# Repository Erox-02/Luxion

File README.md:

# Luxion

Luxion is a custom made drone made with rust unlike standard c++ drones .
It uses a custom pcb, ESP32-S3-WROOM-1U , MPU6500-IMU(breakout as it costs less than the bare), four motor drivers, and a 1S LiPo to power the drone. Also a remote with
same esp module, 2x joysticks connectin to the drone via esp-now .

## Function

It is a remote controlled drone made from absolutely nothing , with 8520 motors and 65mm props it can easily take off with 2+ thrust-mass ratio . It is ideal for mini quadcoptor with mountable sensors ,as it has a lot of gpio's left any sensor can be easily mounted if not too heavy .

## Why it exists

from when i saw the pluto x  , a programable drone with esp 12f and stm32 , i always wanted to make one myself but better and cheaper thts why luxion exists today. I used esp32-s3 instead of 2 mcu's , used esp-now instead of wifi and a lot but the best part i didnt rely on the pluto x's architecture at all .

## Design
---

### 3D Model

> **Notice: All the screws there are 3mm .** 

The recommended range by me is M5x3 mm 

heres a photo tagged:

but for the pcb M1.2x3 mm is totally usable 

#### Drone

You can download the 3d model frm here :
[DOWNLOAD THE 3d MODEL](3d/lux.3mf)

also the  fcstd file is tagged here :

[FCSTD](3d/lux.FCStd)

some photos for the frame :

<table>
  <tr>
    <td></td>
    <td></td>
    <td></td>
  </tr>
</table>

---

#### Remote

You can download the 3d model frm here :

[DOWNLOAD THE 3d MODEL](3d/remote-body.3mf)
[DOWNLOAD THE 3d MODEL](3d/remote-lid.3mf)

===

also the  fcstd file is tagged here :

[FCSTD](3d/remote.FCStd)

Some phots of the remote :

<table>
  <tr>
    <td></td>
    <td></td>
  </tr>
</table>

---

### Schematic
---

#### drone

<table>
  <tr>
    <td></td>
    <td></td>
    <td></td>
  </tr>
  <tr>
    <td></td>
    <td></td>
    <td></td>
  </tr>
  <tr>
    <td></td>
    <td></td>
  </tr>
</table>

---

#### remote
---

<table>
  <tr>
    <td></td>
    <td></td>
  </tr>
  <tr>
    <td></td>
    <td></td>
  </tr>
</table>

### PCB

#### drone

Heres the pcb :

<table>
  <tr>
    <td></td>
    <td></td>
  </tr>
</table>

#### remote

Heres the pcb :

<table>
  <tr>
    <td></td>
    <td></td>
  </tr>
</table>

## Firmware

I have written likely most of the firmware already before getting approved or building the physical drone .

Current stack have :
```
[erox@archbtw luxion]$ tree src 
src
├── filter.rs
├── main.rs
├── motor.rs
├── mpu.rs          
└── pid.rs

1 directory, 5 files
```

the mpu.rs is a custom driver(really basic) for the mpu6050 , the filte* take mpu's data(gyro and acc) then converts tht into yaw roll and pitch , the moto* haved ldec and controlls the motors state , the pid is just pid controller nothing more , and the main.rs integrates them all and runs them when needed either in loop or once .

### Whats remainin?

- esp now impl
- build.rs
- proper pid vals and calibration

## How to assemble

Solder all the components from bom(except the antenna) on the pcb ,
also You might need to solder a jst socket according to your battery
(more detailed explanation after i do it myself first lol)

you can follow this hand drawn diagram(even orphy is better than me)
---

---

another thing to consider, this photo doesnt have all the components placed so this isnt the final pcb(checkt he comps on bom ) , and for the mpu6050 and the bmp , they are supposed to be placed horizontal to the pcb , mpu on the esp farday cage(tested by max imagination, he is a cool dude btw , i saw his Arduino drone on YouTube) and the bmp shld be stacked on top of mpu , it shld give them the least vibration err , still idea but i will be sure after i build it myself lol.

## Credits

This project uses:

- KiCad
- Freecad for 3D renders
- A opensource frame from the link below

[link](https://www.thingiverse.com/thing:5013951)

> It was the reference for my frame i had to rebuild it .

## JLCPCB order

---

---

> the price might fluctuate over time

## BOM

| Part | Quantity | Unit Price (INR) | Unit Price (USD) | Total (INR) | Total (USD) | Link |
|---|---:|---:|---:|---:|---:|---|
| MPU-6050 3-Axis Accelerometer + Gyro | 1 | 151.00 | 1.59 | 151.00 | 1.59 | [Link](https://robu.in/product/mpu-6050-gyro-sensor-2-accelerometer/) |
| PS2 Joystick Module Breakout Sensor | 2 | 39.00 | 0.41 | 78.00 | 0.82 | [Link](https://robu.in/product/joystick-module-ps2-breakout-sensor/) |
| 8520 Magnetic Micro Coreless Motors – 2xCW + 2xCCW pack | 1 | 459.00 | 4.83 | 459.00 | 4.83 | [Link](https://robu.in/product/8520-magnetic-micro-coreless-motor-for-micro-quadcopters-2xcw-2xccw/) |
| 100kΩ 0603 resistor (MOQ) | 30 | 0.34 | 0.004 | 10.20 | 0.11 | [Link](https://robu.in/product/100k-ohm-1-4w-0603-surface-mount-chip-resistor-pack-of-100/) |
| 220Ω 0603 resistor (MOQ) | 30 | 0.34 | 0.004 | 10.20 | 0.11 | [Link](https://robu.in/product/220-ohm-chip-resistor-1-4w-0603-surface-mount-pack-of-100/) |
| 3V Active Electromagnetic Buzzer – pack of 5 | 1 | 21.00 | 0.22 | 21.00 | 0.22 | [Link](https://robu.in/product/3v-active-electromagnetic-buzzer-pack-of-5/) |
| 1206 Surface Mount LED White (MOQ) | 10 | 1.07 | 0.011 | 10.70 | 0.11 | [Link](https://robu.in/product/1206-surface-mount-led-white-50-pcs/) |
| 1206 Surface Mount LED Yellow (MOQ) | 25 | 0.40 | 0.004 | 10.00 | 0.11 | [Link](https://robu.in/product/1206-surface-mount-led-yellow-50pcs/) |
| BMP180 Digital Barometric Pressure Sensor Module | 1 | 33.00 | 0.35 | 33.00 | 0.35 | [Link](https://robu.in/product/bmp180-digital-barometric-pressure-sensor-module/) |
| LWC-2400-DIP-03 (V1.0) Dipole Antenna 2.4 GHz | 2 | 132.00 | 1.39 | 264.00 | 2.78 | [Link](https://robu.in/product/lwc-2400-dip-03-v1-0-dipole-antennas-2-4-ghz/) |
| Bonka 3.7V 600mAh 25C 1S LiPo | 1 | 499.00 | 5.25 | 499.00 | 5.25 | [Link](https://robu.in/product/bonka-3-7v-600mah-25c-1s-lithium-polymer-battery-pack/) |
| 22µF 16V 1206 X5R capacitor (MOQ) | 28 | 0.36 | 0.004 | 10.08 | 0.11 | [Link](https://robu.in/product/1206x226k160ct-samsung-smd-multilayer-ceramic-capacitor-22-%c2%b5f-16-v-1206-3216-metric-%c2%b1-10-x5r/) |
| 100nF 0402 X7R capacitor (MOQ) | 100 | 0.10 | 0.001 | 10.00 | 0.11 | [Link](https://robu.in/product/im02b104k250nb-fh-smd-multilayer-ceramic-capacitor-0-1-%c2%b5f100-nf-25-v-0402-1005-metric-%c2%b1-10-x7r-cl/) |
| 10kΩ 0603 resistor (MOQ) | 15 | 0.68 | 0.007 | 10.20 | 0.11 | [Link](https://robu.in/product/ac0603fr-0710kl-yageo-res-thick-film-0603-10k-ohm-1-0-1w1-10w-%c2%b1100ppm-c-pad-smd-t-r-automotive-aec-q200/) |
| ESP32-S3-WROOM-1U-N16R8 | 2 | 469.00 | 4.94 | 938.00 | 9.87 | [Link](https://robu.in/product/espressif-esp32-s3-wroom-1u-n16r8-module/) |
| 10µF 10V 0805 X5R capacitor (MOQ) | 22 | 0.47 | 0.005 | 10.34 | 0.11 | [Link](https://robu.in/product/cs2012x5r106m100nre-samwha-10v-x5r-0805-multilayer-ceramic-capacitors-mlcc-smd-smt-rohs/) |
| SRN8040-1R5Y 1.5µH 7A inductor | 1 | 23.00 | 0.24 | 23.00 | 0.24 | [Link](https://robu.in/product/srn8040-1r5y-bourns-srn8040-1r5y-power-inductor-smd-1-5-%c2%b5h-7-a-shielded-8-2-a-srn8040-series/) |
| BL5612-BL H-Bridge Motor Driver IC | 4 | 41.00 | 0.43 | 164.00 | 1.73 | [Link](https://robu.in/product/bl5612-blshanghai-belling-h-bridge-motor-driver-ic-1-5a-sop-8/) |
| 560kΩ 0603 resistor (MOQ) | 28 | 0.36 | 0.004 | 10.08 | 0.11 | [Link](https://robu.in/product/erjp03j564v-panasonic-200mw-thick-film-resistors-%c2%b15-%c2%b1200ppm-%e2%84%83-560k%cf%89-0603-chip-resistor-surface-mount-rohs/) |
| 5.6kΩ 0603 resistor (MOQ) | 28 | 0.37 | 0.004 | 10.36 | 0.11 | [Link](https://robu.in/product/erj3geyj562v-panasonic-100mw-thick-film-resistors-%c2%b15-%c2%b1200ppm-%e2%84%83-5-6k%cf%89-0603-chip-resistor-surface-mount-rohs/) |
| TYPE-C-31-M-12 Hroparts 5A 1 16P Female Type-C SMD USB Connector | 2 | 26.00 | 0.27 | 52.00 | 0.55 | [Link](https://robu.in/product/type-c-31-m-12-hroparts-5a-1-16p-female-type-c-smd-usb-connectors-rohs/) |
| JST 2P Male + Female Terminal Connection Socket | 1 | 30.00 | 0.32 | 30.00 | 0.32 | [Link](https://robu.in/product/jst-2p-malefemale-terminal-connection-socket/) |
| TPS63020DSJR | 2 | 178.00 | 1.87 | 356.00 | 3.75 | [Link](https://robu.in/product/tps63020dsjr-texas-instruments-boost-type-adjustable-1-2v5-5v-1-8v5-5v-vson-14-ep3x4-dc-dc-converters-rohs/) |
| **Drone PCB** | 1 | 769.50 | **8.10** | 769.50 | **8.10** | — |
| **Remote PCB** | 1 | 760.00 | **8.00** | 760.00 | **8.00** | — |
| **Drone Frame** | 1 | 224.20 | **2.36** | 224.20 | **2.36** | — |
| **TOTAL** | | | | **4,923.86** | **51.83** | |

> i used 95inr = 1$ , also the prices gonna change soon .

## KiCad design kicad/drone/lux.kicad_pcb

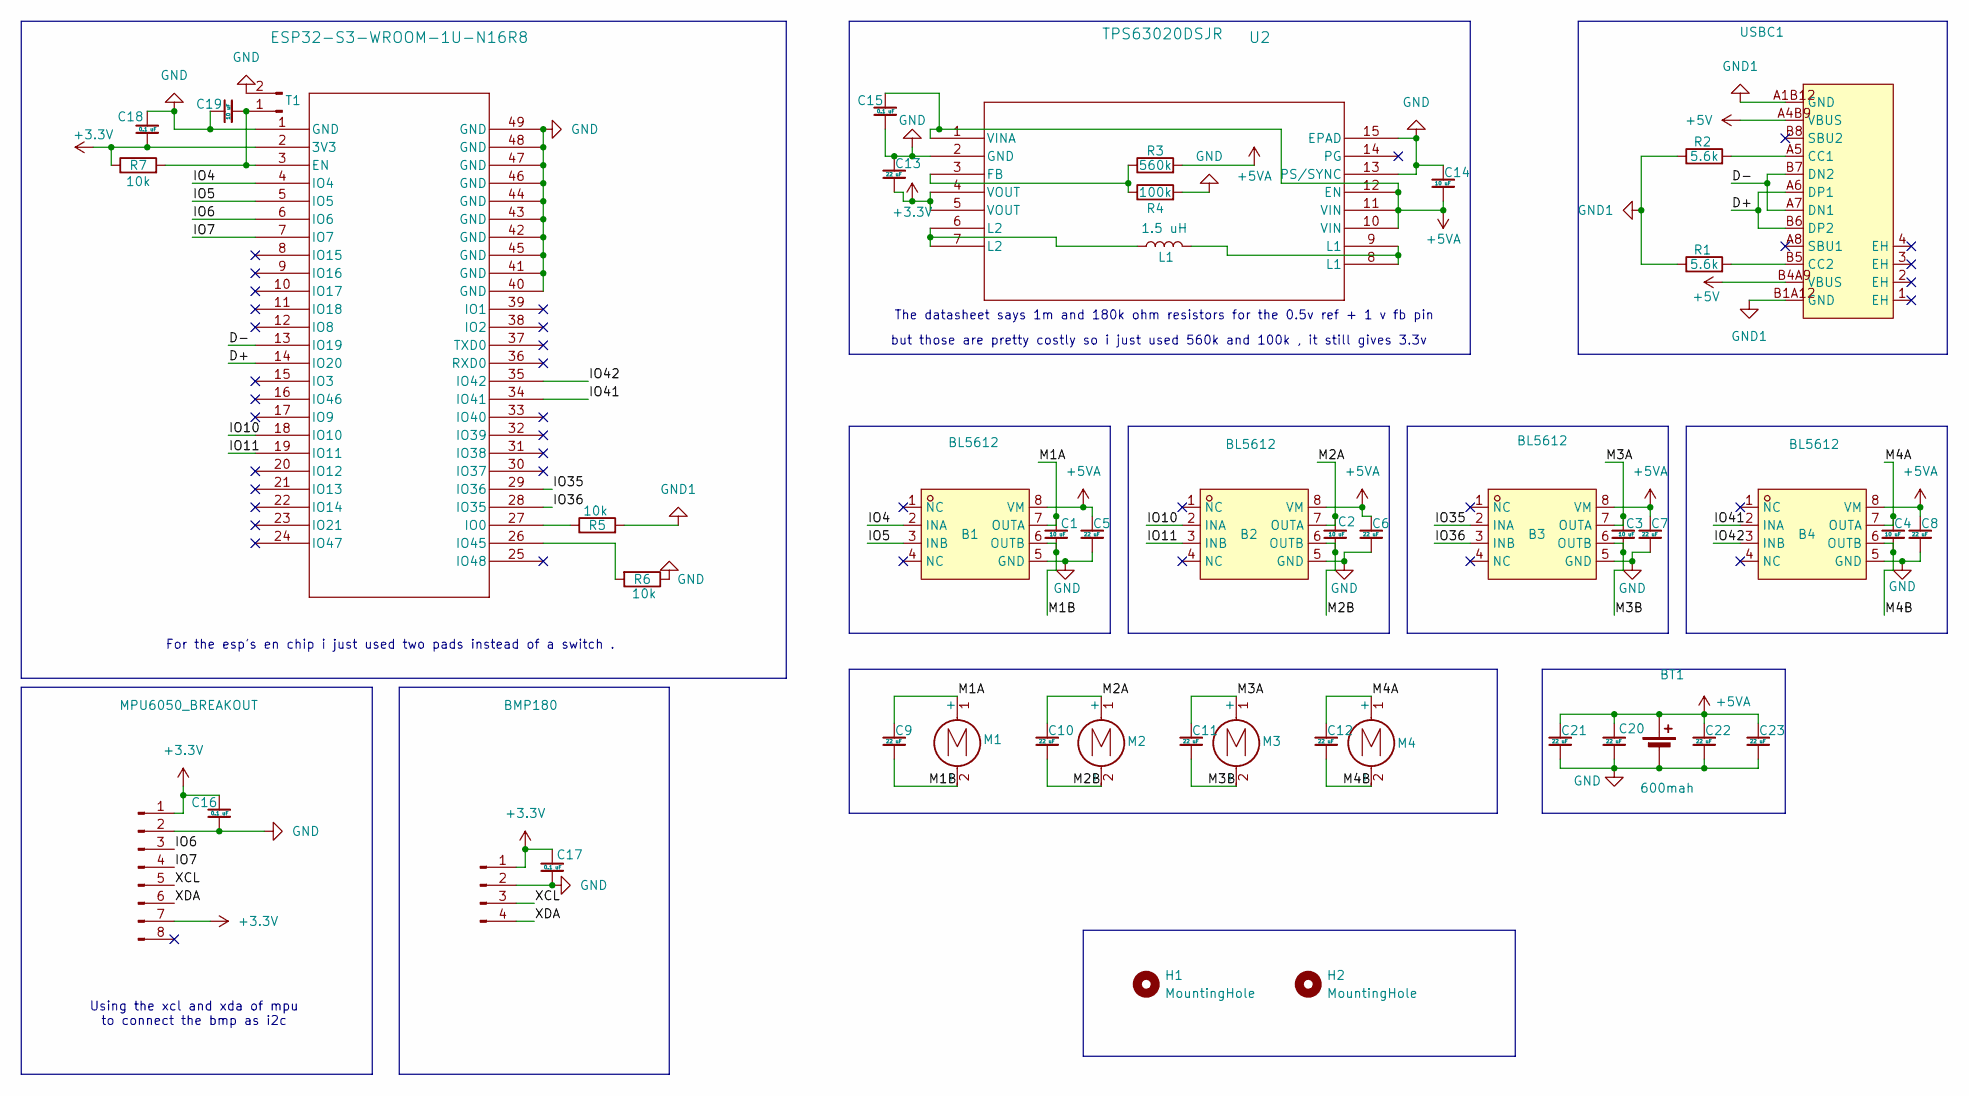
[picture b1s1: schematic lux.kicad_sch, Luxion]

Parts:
B1, B2, B3, B4: BL5612; SOP-8_L4.9-W3.9-P1.27-LS6.0-BL; MPN BL5612; LCSC Part C2841019
BMP1: BMP180; Hirose_DF13-04P-1.25DSA_1x04_P1.25mm_Vertical
BT1: 600mah; PinHeader_1x02_P2.54mm_Vertical
C1, C2, C3, C4, C14, C19: 10 uF; C_0805_2012Metric
C5, C6, C7, C8, C9, C10, C11, C12, C13, C20, C21, C22, C23: 22 uF; C_1206_3216Metric
C15, C16, C17, C18: 0.1 uF; C_0402_1005Metric
H1, H2: MountingHole; MountingHole_2.5mm
L1: 1.5 uH; L_Bourns-SRN8040_8x8.15mm
M1, M2, M3, M4: Motor_DC; JST_PH_B2B-PH-K_1x02_P2.00mm_Vertical
MPU1: MPU6050_BREAKOUT; Hirose_DF13-08P-1.25DSA_1x08_P1.25mm_Vertical
R1, R2: 5.6k; R_0603_1608Metric
R3: 560k; R_0603_1608Metric
R4: 100k; R_0603_1608Metric
R5, R6, R7: 10k; R_0603_1608Metric
T1: trace; C_1206_3216Metric
U1: ESP32-S3-WROOM-1U-N16R8; ESP32-S3-WROOM-1U_EXP
U2: TPS63020DSJR; DSJ14_2P85X1P58
USBC1: TYPE-C-31-M-12; USB-C_SMD-TYPE-C-31-M-12_1; MPN TYPE-C-31-M-12; LCSC Part C165948

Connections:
+3.3V: BMP1.1, C13.2, C16.1, C17.1, C18.2, MPU1.1, MPU1.7, R7.1, U1.2 (3V3), U2.4 (VOUT), U2.5 (VOUT)
+5V: USBC1.A4B9 (VBUS), USBC1.B4A9 (VBUS)
+5VA: B1.8 (VM), B2.8 (VM), B3.8 (VM), B4.8 (VM), BT1.1 (+), C5.1, C6.1, C7.1, C8.1, C14.2, C15.1, C20.1, C21.1, C22.1, C23.1, R3.2, U2.1 (VINA), U2.10 (VIN), U2.11 (VIN), U2.12 (EN)
/D+: U1.14 (IO20), USBC1.A6 (DP1), USBC1.B6 (DP2)
/D-: U1.13 (IO19), USBC1.A7 (DN1), USBC1.B7 (DN2)
/IO4: B1.2 (INA), U1.4 (IO4)
/IO5: B1.3 (INB), U1.5 (IO5)
/IO6: MPU1.3, U1.6 (IO6)
/IO7: MPU1.4, U1.7 (IO7)
/IO10: B2.2 (INA), U1.18 (IO10)
/IO11: B2.3 (INB), U1.19 (IO11)
/IO35: B3.2 (INA), U1.29 (IO36)
/IO36: B3.3 (INB), U1.28 (IO35)
/IO41: B4.2 (INA), U1.34 (IO41)
/IO42: B4.3 (INB), U1.35 (IO42)
/M1A: B1.7 (OUTA), C1.1, C9.1, M1.1 (+)
/M1B: B1.6 (OUTB), C1.2, C9.2, M1.2 (-)
/M2A: B2.7 (OUTA), C2.1, C10.1, M2.1 (+)
/M2B: B2.6 (OUTB), C2.2, C10.2, M2.2 (-)
/M3A: B3.7 (OUTA), C3.1, C11.1, M3.1 (+)
/M3B: B3.6 (OUTB), C3.2, C11.2, M3.2 (-)
/M4A: B4.7 (OUTA), C4.1, C12.1, M4.1 (+)
/M4B: B4.6 (OUTB), C4.2, C12.2, M4.2 (-)
/XCL: BMP1.3, MPU1.5
/XDA: BMP1.4, MPU1.6
GND: B1.5 (GND), B2.5 (GND), B3.5 (GND), B4.5 (GND), BMP1.2, BT1.2 (-), C5.2, C6.2, C7.2, C8.2, C13.1, C14.1, C15.2, C16.2, C17.2, C18.1, C19.1, C20.2, C21.2, C22.2, C23.2, MPU1.2, R4.2, R6.1, T1.2, U1.1 (GND), U1.40 (GND), U1.41 (GND), U1.42 (GND), U1.43 (GND), U1.44 (GND), U1.45 (GND), U1.46 (GND), U1.47 (GND), U1.48 (GND), U1.49 (GND), U2.2 (GND), U2.13 (PS/SYNC), U2.15 (EPAD)
GND1: R1.1, R2.1, R5.2, USBC1.A1B12 (GND), USBC1.B1A12 (GND)
unnamed: L1.1, U2.6 (L2), U2.7 (L2)
unnamed: L1.2, U2.8 (L1), U2.9 (L1)
unnamed: C19.2, R7.2, T1.1, U1.3 (EN)
unnamed: R5.1, U1.27 (IO0)
unnamed: R6.2, U1.26 (IO45)
unnamed: R3.1, R4.1, U2.3 (FB)
unnamed: R2.2, USBC1.A5 (CC1)
unnamed: R1.2, USBC1.B5 (CC2)

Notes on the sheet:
The datasheet says 1m and 180k ohm resistors for the 0.5v ref + 1 v fb pin
Using the xcl and xda of mpu to connect the bmp as i2c
For the esp's en chip i just used two pads instead of a switch .
but those are pretty costly so i just used 560k and 100k , it still gives 3.3v

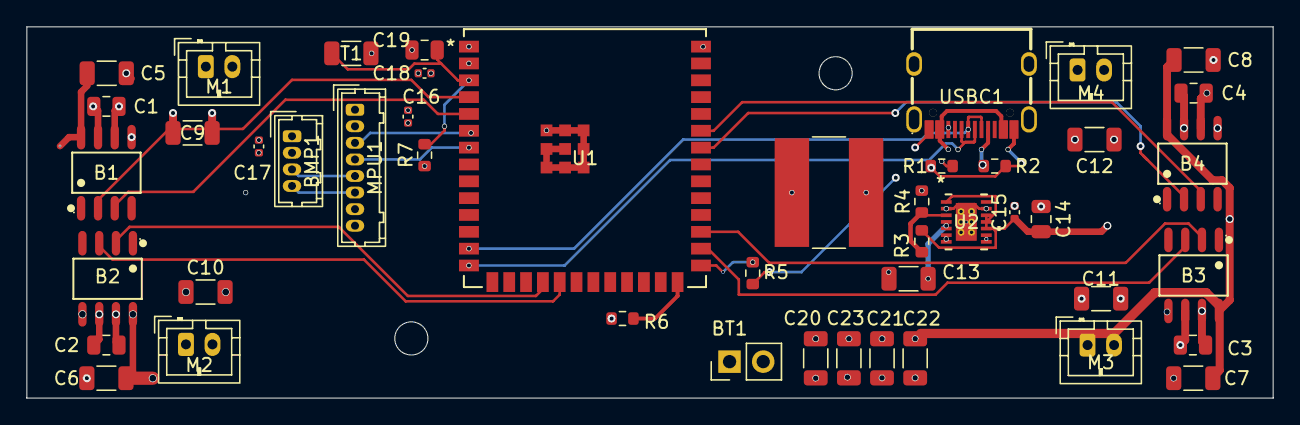
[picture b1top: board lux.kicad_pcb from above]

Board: 4 copper layers, 94.0 x 28.0 mm, 50 parts (0 on the bottom side), 35 nets.

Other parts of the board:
H1#2, H2#2: MountingHole; MountingHole_2.5mm

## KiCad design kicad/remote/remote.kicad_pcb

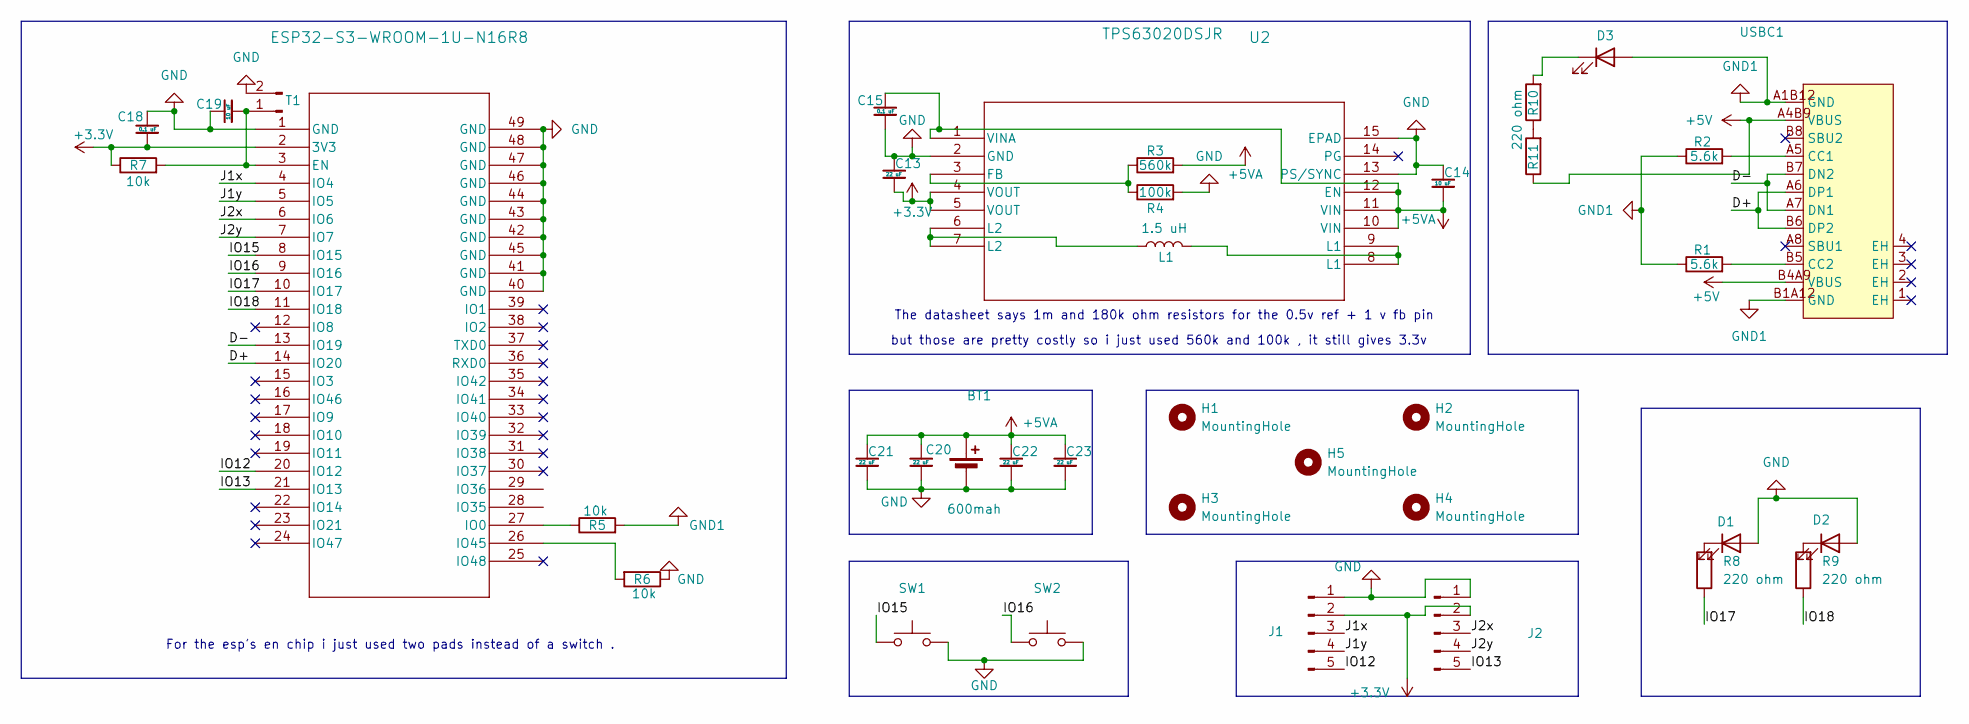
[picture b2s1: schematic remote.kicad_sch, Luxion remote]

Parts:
BT1: 600mah; PinHeader_1x02_P2.54mm_Vertical
C13, C20, C21, C22, C23: 22 uF; C_1206_3216Metric
C14, C19: 10 uF; C_0805_2012Metric
C15, C18: 0.1 uF; C_0402_1005Metric
D1, D3: Yellow; LED_1206_3216Metric
D2: WHITE; LED_1206_3216Metric
H1, H2, H3, H4, H5: MountingHole; MountingHole_2.5mm
J1, J2: joystick; PinHeader_1x05_P2.54mm_Vertical
L1: 1.5 uH; L_Bourns-SRN8040_8x8.15mm
R1, R2: 5.6k; R_0603_1608Metric
R3: 560k; R_0603_1608Metric
R4: 100k; R_0603_1608Metric
R5, R6, R7: 10k; R_0603_1608Metric
R8, R9, R10, R11: 220 ohm; R_0603_1608Metric
SW1, SW2: sw; SW_PUSH_6mm_H5mm
T1: trace; C_1206_3216Metric
U1: ESP32-S3-WROOM-1U-N16R8; ESP32-S3-WROOM-1U_EXP
U2: TPS63020DSJR; DSJ14_2P85X1P58
USBC1: TYPE-C-31-M-12; USB-C_SMD-TYPE-C-31-M-12_1; MPN TYPE-C-31-M-12; LCSC Part C165948

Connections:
+3.3V: C13.2, C18.2, J1.2, J2.2, R7.1, U1.2 (3V3), U2.4 (VOUT), U2.5 (VOUT)
+5V: R11.1, USBC1.A4B9 (VBUS), USBC1.B4A9 (VBUS)
+5VA: BT1.1 (+), C14.2, C15.1, C20.1, C21.1, C22.1, C23.1, R3.2, U2.1 (VINA), U2.10 (VIN), U2.11 (VIN), U2.12 (EN)
/D+: U1.14 (IO20), USBC1.A6 (DP1), USBC1.B6 (DP2)
/D-: U1.13 (IO19), USBC1.A7 (DN1), USBC1.B7 (DN2)
/IO12: J1.5, U1.20 (IO12)
/IO13: J2.5, U1.21 (IO13)
/IO15: SW1.1, U1.8 (IO15)
/IO16: SW2.1, U1.9 (IO16)
/IO17: R8.1, U1.10 (IO17)
/IO18: R9.1, U1.11 (IO18)
/J1x: J1.3, U1.4 (IO4)
/J1y: J1.4, U1.5 (IO5)
/J2x: J2.3, U1.6 (IO6)
/J2y: J2.4, U1.7 (IO7)
GND: BT1.2 (-), C13.1, C14.1, C15.2, C18.1, C19.1, C20.2, C21.2, C22.2, C23.2, D1.2 (A), D2.2 (A), J1.1, J2.1, R4.2, R6.1, SW1.2, SW2.2, T1.2, U1.1 (GND), U1.40 (GND), U1.41 (GND), U1.42 (GND), U1.43 (GND), U1.44 (GND), U1.45 (GND), U1.46 (GND), U1.47 (GND), U1.48 (GND), U1.49 (GND), U2.2 (GND), U2.13 (PS/SYNC), U2.15 (EPAD)
GND1: D3.2 (A), R1.1, R2.1, R5.2, USBC1.A1B12 (GND), USBC1.B1A12 (GND)
unnamed: D1.1 (K), R8.2
unnamed: D2.1 (K), R9.2
unnamed: D3.1 (K), R10.2
unnamed: L1.1, U2.6 (L2), U2.7 (L2)
unnamed: L1.2, U2.8 (L1), U2.9 (L1)
unnamed: R10.1, R11.2
unnamed: C19.2, R7.2, T1.1, U1.3 (EN)
unnamed: R5.1, U1.27 (IO0)
unnamed: R6.2, U1.26 (IO45)
unnamed: R3.1, R4.1, U2.3 (FB)
unnamed: R2.2, USBC1.A5 (CC1)
unnamed: R1.2, USBC1.B5 (CC2)

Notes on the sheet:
The datasheet says 1m and 180k ohm resistors for the 0.5v ref + 1 v fb pin
For the esp's en chip i just used two pads instead of a switch .
but those are pretty costly so i just used 560k and 100k , it still gives 3.3v

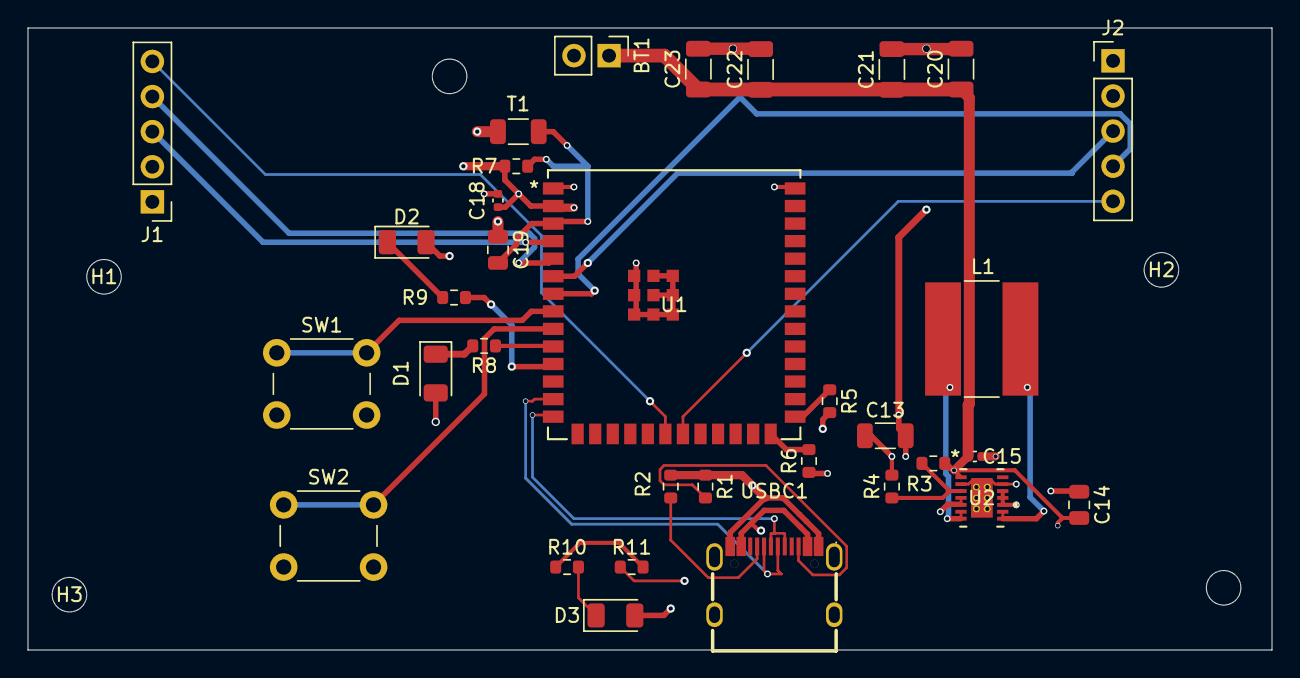
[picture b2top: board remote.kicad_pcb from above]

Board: 4 copper layers, 90.0 x 45.0 mm, 38 parts (0 on the bottom side), 29 nets.
